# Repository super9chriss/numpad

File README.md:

# Custom numpad using an rp2040

A numpad which i can place next to my existing keyboard or remove depending on what im doing, it uses a RP2040 controller with QMK firmware.

<div align="center">

</div>

## BOM

| Component | Quantity | Description | Link | Cost |
| :--- | :---: | :--- | :--- | :--- |
| **MCU** | 1 | Seeed XIAO RP2040 |https://www.tinytronics.nl/en/development-boards/microcontroller-boards/others/seeed-studio-seeeduino-xiao-rp2040-dual-core-cortex-m0-separate-headers | €7.00
| **Switches** | 16 | Cherry MX compatible switches | https://www.amazon.nl/mechanische-toetsenbordschakelaars-reserveonderdelen-reserveschakelaar-gamingtoetsenbord/dp/B0FH1J46V5 | €9.79
| **Keycaps** | 16 | DSA Profile (Blank) | https://www.amazon.nl/Paopaoldm-Engraving-Sublimation-Switches-Keyboard/dp/B0D3FR1HT5| €8.34
| **PCB** | 1 | Custom Numpad PCB | https://cart.jlcpcb.com/quote?stencilLayer=2&stencilWidth=100&stencilLength=100&stencilCounts=5&plateType&spm=Jlcpcb.Homepage.1010 | €18.79
| **Inserts** | 4 | M3 Heatset Inserts | https://www.bitsandparts.nl/Draadinzetstuk-M3-x-4-x-4-p1929600?gad_source=1&gad_campaignid=17339301268&gbraid=0AAAAADpItpeM5ppLxZ7FQfrTrApre5PML&gclid=Cj0KCQiA6Y7KBhCkARIsAOxhqtOuZc5zMjiW9-lEVaj6UW_oBEvaZ3dtExOxGxcrMgOVI5ki9B38r9saAgo3EALw_wcB | €0.80
| **Screws** | 4 | M3x16 Bolts | https://www.hornbach.nl/p/dresselhaus-lenskopschroef-kruis-m3x16-mm-phillips-ph2-din-7985-rvs-a2-100-stuks/6836143/ | €0.18
| **Total** |  |  |  | **€44.90** |

## PCB and schematic

I made a custom PCB with a 4x4 keyboard matrix and a rotary encoder so i can change my volume.

| **PCB Layout** | **Schematic** |
| :---: | :---: |
| |  |
||

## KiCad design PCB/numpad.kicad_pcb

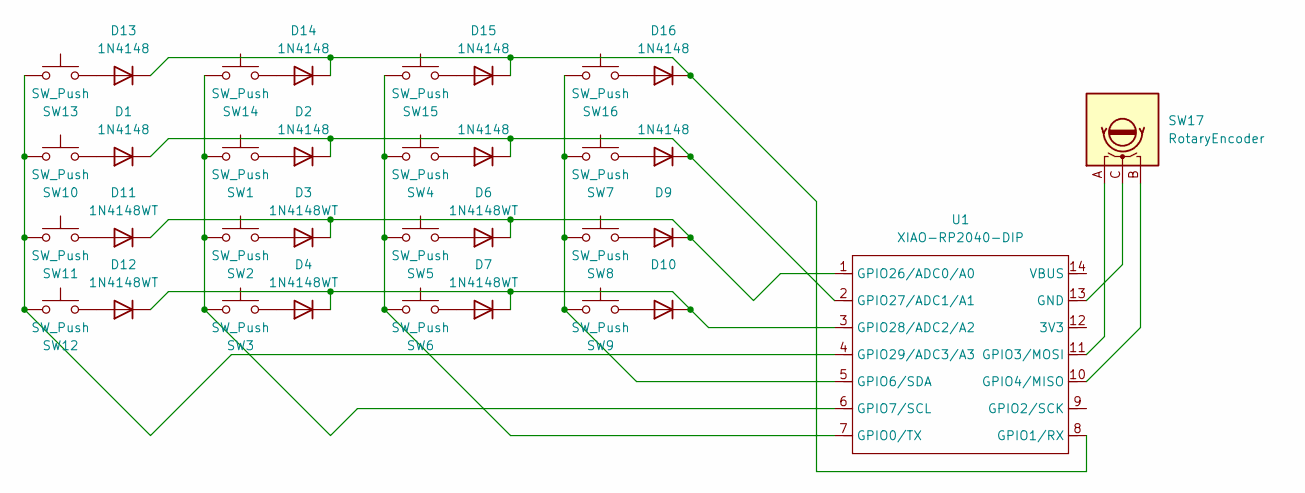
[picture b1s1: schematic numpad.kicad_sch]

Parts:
D1, D2, D5, D8, D13, D14, D15, D16: 1N4148; D_DO-35_SOD27_P7.62mm_Horizontal
D3, D4, D6, D7, D9, D10, D11, D12: 1N4148WT; D_DO-35_SOD27_P7.62mm_Horizontal
SW1, SW2, SW3, SW4, SW5, SW6, SW7, SW8, SW9, SW10, SW11, SW12, SW13, SW14, SW15, SW16: SW_Push; SW_Cherry_MX_1.00u_PCB
SW17: RotaryEncoder; RotaryEncoder_Alps_EC11E-Switch_Vertical_H20mm
U1: XIAO-RP2040-DIP

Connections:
unnamed: D1.2 (A), SW10.2
unnamed: D1.1 (K), D2.1 (K), D5.1 (K), D8.1 (K), U1.2 (GPIO27/ADC1/A1)
unnamed: D2.2 (A), SW1.2
unnamed: D3.2 (A), SW2.2
unnamed: D4.2 (A), SW3.2
unnamed: D5.2 (A), SW4.2
unnamed: D6.2 (A), SW5.2
unnamed: D7.2 (A), SW6.2
unnamed: D8.2 (A), SW7.2
unnamed: D9.2 (A), SW8.2
unnamed: D10.2 (A), SW9.2
unnamed: D4.1 (K), D7.1 (K), D10.1 (K), D12.1 (K), U1.3 (GPIO28/ADC2/A2)
unnamed: D11.2 (A), SW11.2
unnamed: D3.1 (K), D6.1 (K), D9.1 (K), D11.1 (K), U1.1 (GPIO26/ADC0/A0)
unnamed: D12.2 (A), SW12.2
unnamed: D13.2 (A), SW13.2
unnamed: D13.1 (K), D14.1 (K), D15.1 (K), D16.1 (K), U1.8 (GPIO1/RX)
unnamed: D14.2 (A), SW14.2
unnamed: D15.2 (A), SW15.2
unnamed: D16.2 (A), SW16.2
unnamed: SW17.C, U1.13 (GND)
unnamed: SW4.1, SW5.1, SW6.1, SW15.1, U1.7 (GPIO0/TX)
unnamed: SW17.A, U1.11 (GPIO3/MOSI)
unnamed: SW17.B, U1.10 (GPIO4/MISO)
unnamed: SW7.1, SW8.1, SW9.1, SW16.1, U1.5 (GPIO6/SDA)
unnamed: SW1.1, SW2.1, SW3.1, SW14.1, U1.6 (GPIO7/SCL)
unnamed: SW10.1, SW11.1, SW12.1, SW13.1, U1.4 (GPIO29/ADC3/A3)

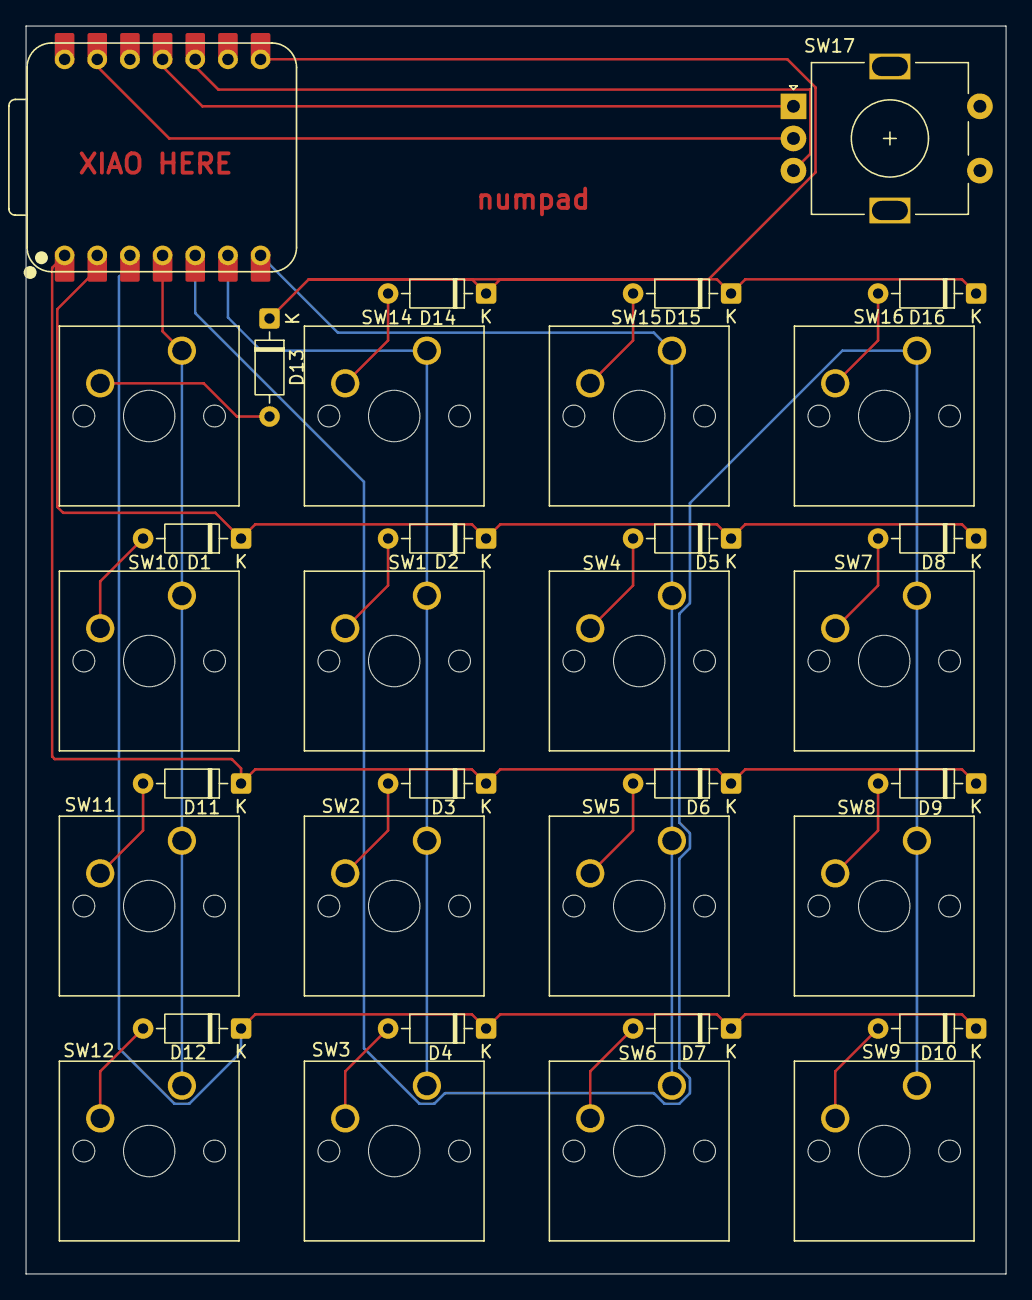
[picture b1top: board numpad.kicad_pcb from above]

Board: 2 copper layers, 76.2 x 97.0 mm, 34 parts (0 on the bottom side), 27 nets.

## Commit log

2025-12-04 Schematic + PCB
